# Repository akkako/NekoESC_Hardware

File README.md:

# NekoESC Hardware design repo

NekoESC V1 is a 4-in-1 ESC based on AM32 firmware.

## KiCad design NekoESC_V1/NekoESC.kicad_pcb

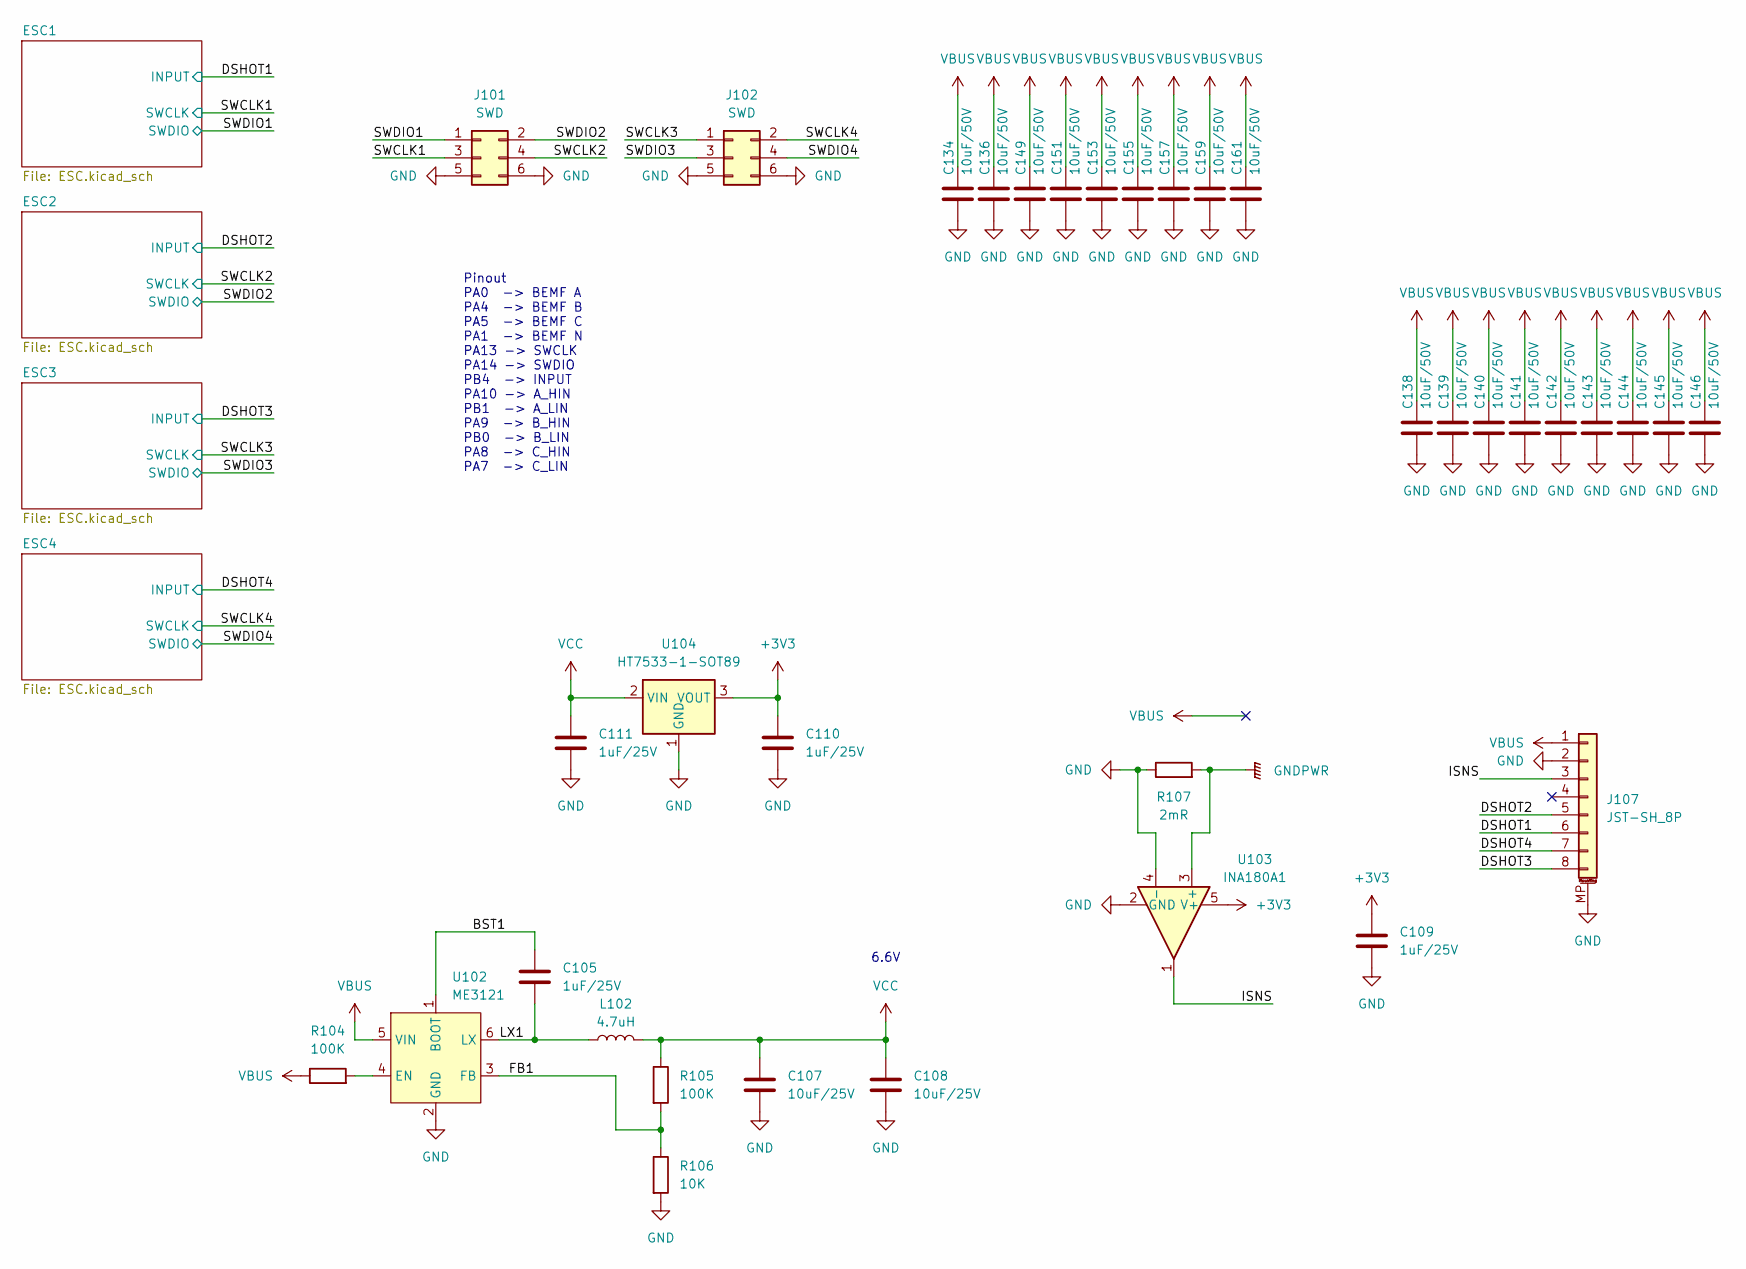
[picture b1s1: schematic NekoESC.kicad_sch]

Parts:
C105, C109, C110, C111: 1uF/25V; C_0402
C107, C108: 10uF/25V; C_0603_1608Metric
C134, C136, C138, C139, C140, C141, C142, C143, C144, C145, C146, C149, C151, C153, C155, C157, C159, C161: 10uF/50V; C_1206
J101, J102: SWD; PinHeader_2x03_P1.27mm_Vertical
J107: JST-SH_8P; JST_SH_SM08B-SRSS-TB_1x08-1MP_P1.00mm_Horizontal
L102: 4.7uH; L_Sunlord_SWPA3015S
R104, R105: 100K; R_0402
R106: 10K; R_0402
R107: 2mR; R_1206_3216Metric
U102: ME3121; SOT-23-6
U103: INA180A1; SOT-23-5
U104: HT7533-1-SOT89; SOT-89-3

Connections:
+3V3: C109.1, C110.1, U103.5 (V+), U104.3 (VOUT); also elsewhere on the board
/BST1: C105.1, U102.1 (BOOT)
/DSHOT1: J107.6; also elsewhere on the board
/DSHOT2: J107.5; also elsewhere on the board
/DSHOT3: J107.8; also elsewhere on the board
/DSHOT4: J107.7; also elsewhere on the board
/FB1: R105.2, R106.1, U102.3 (FB)
/ISNS: J107.3, U103.1
/LX1: C105.2, L102.1, U102.6 (LX)
/SWCLK1: J101.3; also elsewhere on the board
/SWCLK2: J101.4; also elsewhere on the board
/SWCLK3: J102.1; also elsewhere on the board
/SWCLK4: J102.2; also elsewhere on the board
/SWDIO1: J101.1; also elsewhere on the board
/SWDIO2: J101.2; also elsewhere on the board
/SWDIO3: J102.3; also elsewhere on the board
/SWDIO4: J102.4; also elsewhere on the board
GND: C107.2, C108.2, C109.2, C110.2, C111.2, C134.2, C136.2, C138.2, C139.2, C140.2, C141.2, C142.2, C143.2, C144.2, C145.2, C146.2, C149.2, C151.2, C153.2, C155.2, C157.2, C159.2, C161.2, J101.5, J101.6, J102.5, J102.6, J107.2, J107.MP (MountPin), R106.2, R107.1, U102.2 (GND), U103.2 (GND), U103.4 (-), U104.1 (GND); also elsewhere on the board
GNDPWR: R107.2, U103.3 (+)
unnamed: R104.2, U102.4 (EN)
VBUS: C134.1, C136.1, C138.1, C139.1, C140.1, C141.1, C142.1, C143.1, C144.1, C145.1, C146.1, C149.1, C151.1, C153.1, C155.1, C157.1, C159.1, C161.1, J107.1, R104.1, U102.5 (VIN); also elsewhere on the board
VCC: C107.1, C108.1, C111.1, L102.2, R105.1, U104.2 (VIN); also elsewhere on the board

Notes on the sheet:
6.6V
Pinout PA0 -> BEMF A PA4 -> BEMF B PA5 -> BEMF C PA1 -> BEMF N PA13 -> SWCLK PA14 -> SWDIO PB4 -> INPUT PA10 -> A_HIN PB1 -> A_LIN PA9 -> B_HIN PB0 -> B_LIN PA8 -> C_HIN PA7 -> C_LIN

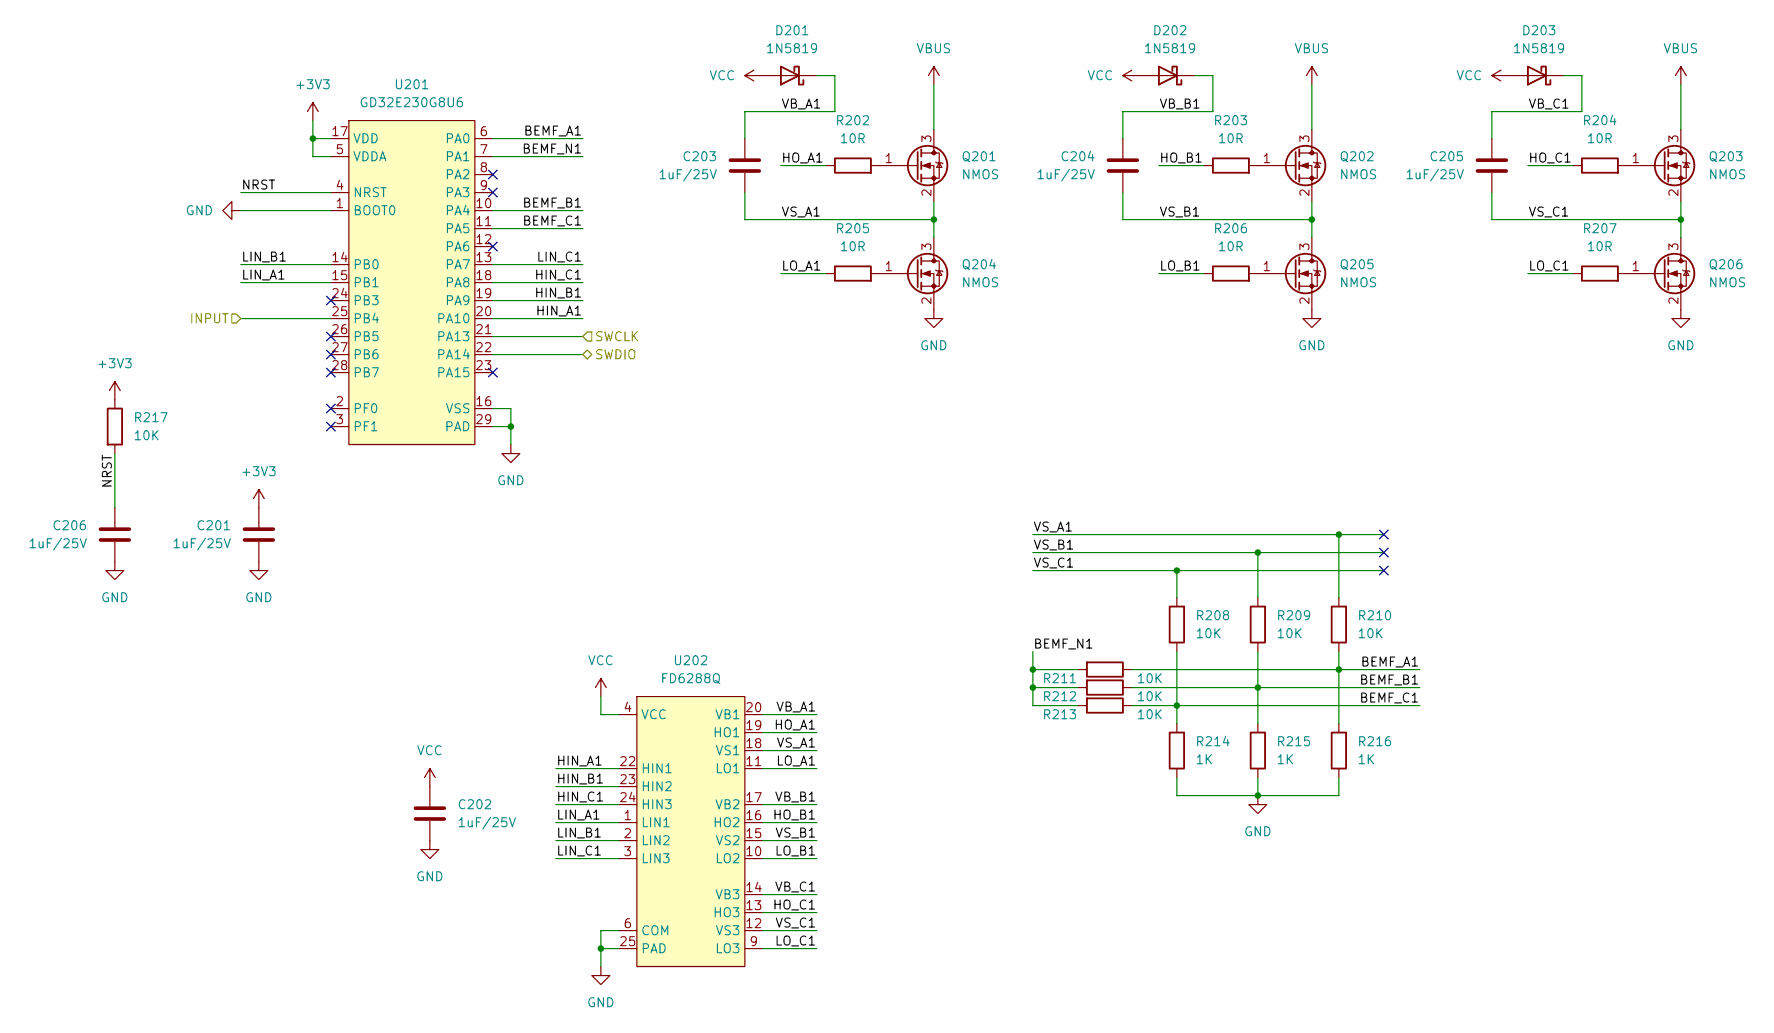
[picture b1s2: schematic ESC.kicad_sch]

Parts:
C201, C202, C203, C204, C205, C206: 1uF/25V; C_0402
D201, D202, D203: 1N5819; D_SOD-323
Q201, Q202, Q203, Q204, Q205, Q206: NMOS; DFN-8_3x3_MOS_GSD
R202, R203, R204, R205, R206, R207: 10R; R_0402
R208, R209, R210, R211, R212, R213, R217: 10K; R_0402
R214, R215, R216: 1K; R_0402
U201: GD32E230G8U6; WQFN-28-1EP_4x4mm_P0.4mm_EP2.7x2.7mm
U202: FD6288Q; QFN-24-1EP_4x4mm_P0.5mm_EP2.7x2.7mm

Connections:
+3V3: C201.1, R217.1, U201.5 (VDDA), U201.17 (VDD); also elsewhere on the board
/DSHOT1: U201.25 (PB4); also elsewhere on the board
/ESC1/BEMF_A1: R210.1, R211.1, R216.2, U201.6 (PA0)
/ESC1/BEMF_B1: R209.1, R212.1, R215.2, U201.10 (PA4)
/ESC1/BEMF_C1: R208.1, R213.1, R214.2, U201.11 (PA5)
/ESC1/BEMF_N1: R211.2, R212.2, R213.2, U201.7 (PA1)
/ESC1/HIN_A1: U201.20 (PA10), U202.22 (HIN1)
/ESC1/HIN_B1: U201.19 (PA9), U202.23 (HIN2)
/ESC1/HIN_C1: U201.18 (PA8), U202.24 (HIN3)
/ESC1/HO_A1: R202.1, U202.19 (HO1)
/ESC1/HO_B1: R203.1, U202.16 (HO2)
/ESC1/HO_C1: R204.1, U202.13 (HO3)
/ESC1/LIN_A1: U201.15 (PB1), U202.1 (LIN1)
/ESC1/LIN_B1: U201.14 (PB0), U202.2 (LIN2)
/ESC1/LIN_C1: U201.13 (PA7), U202.3 (LIN3)
/ESC1/LO_A1: R205.1, U202.11 (LO1)
/ESC1/LO_B1: R206.1, U202.10 (LO2)
/ESC1/LO_C1: R207.1, U202.9 (LO3)
/ESC1/NRST: C206.1, R217.2, U201.4 (NRST)
/ESC1/VB_A1: C203.1, D201.1 (K), U202.20 (VB1)
/ESC1/VB_B1: C204.1, D202.1 (K), U202.17 (VB2)
/ESC1/VB_C1: C205.1, D203.1 (K), U202.14 (VB3)
/ESC1/VS_A1: C203.2, Q201.2 (S), Q204.3 (D), R210.2, U202.18 (VS1)
/ESC1/VS_B1: C204.2, Q202.2 (S), Q205.3 (D), R209.2, U202.15 (VS2)
/ESC1/VS_C1: C205.2, Q203.2 (S), Q206.3 (D), R208.2, U202.12 (VS3)
/SWCLK1: U201.21 (PA13); also elsewhere on the board
/SWDIO1: U201.22 (PA14); also elsewhere on the board
GND: C201.2, C202.2, C206.2, Q204.2 (S), Q205.2 (S), Q206.2 (S), R214.1, R215.1, R216.1, U201.1 (BOOT0), U201.16 (VSS), U201.29 (PAD), U202.6 (COM), U202.25 (PAD); also elsewhere on the board
unnamed: Q201.1 (G), R202.2
unnamed: Q202.1 (G), R203.2
unnamed: Q203.1 (G), R204.2
unnamed: Q204.1 (G), R205.2
unnamed: Q205.1 (G), R206.2
unnamed: Q206.1 (G), R207.2
VBUS: Q201.3 (D), Q202.3 (D), Q203.3 (D); also elsewhere on the board
VCC: C202.1, D201.2 (A), D202.2 (A), D203.2 (A), U202.4 (VCC); also elsewhere on the board

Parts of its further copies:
C301, C302, C303, C304, C305, C306, C401, C402, C403, C404, C405, C406, C501, C502, C503, C504, C505, C506: 1uF/25V; C_0402
D301, D302, D303, D401, D402, D403, D501, D502, D503: 1N5819; D_SOD-323
Q301, Q302, Q303, Q304, Q305, Q306, Q401, Q402, Q403, Q404, Q405, Q406, Q501, Q502, Q503, Q504, Q505, Q506: NMOS; DFN-8_3x3_MOS_GSD
R218, R219, R220, R308, R309, R310, R311, R312, R313, R408, R409, R410, R411, R412, R413, R508, R509, R510, R511, R512, R513: 10K; R_0402
R301, R302, R303, R305, R306, R307, R401, R402, R403, R405, R406, R407, R501, R502, R503, R505, R506, R507: 10R; R_0402
R314, R315, R316, R414, R415, R416, R514, R515, R516: 1K; R_0402
U301, U401, U501: GD32E230G8U6; WQFN-28-1EP_4x4mm_P0.4mm_EP2.7x2.7mm
U302, U402, U502: FD6288Q; QFN-24-1EP_4x4mm_P0.5mm_EP2.7x2.7mm

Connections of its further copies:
+3V3: C304.1, C404.1, C504.1, R218.1, R219.1, R220.1, U301.5 (VDDA), U301.17 (VDD), U401.5 (VDDA), U401.17 (VDD), U501.5 (VDDA), U501.17 (VDD); also elsewhere on the board
/DSHOT2: U301.25 (PB4); also elsewhere on the board
/DSHOT3: U401.25 (PB4); also elsewhere on the board
/DSHOT4: U501.25 (PB4); also elsewhere on the board
/ESC2/BEMF_A1: R310.1, R311.1, R316.2, U301.6 (PA0)
/ESC2/BEMF_B1: R309.1, R312.1, R315.2, U301.10 (PA4)
/ESC2/BEMF_C1: R308.1, R313.1, R314.2, U301.11 (PA5)
/ESC2/BEMF_N1: R311.2, R312.2, R313.2, U301.7 (PA1)
/ESC2/HIN_A1: U301.20 (PA10), U302.22 (HIN1)
/ESC2/HIN_B1: U301.19 (PA9), U302.23 (HIN2)
/ESC2/HIN_C1: U301.18 (PA8), U302.24 (HIN3)
/ESC2/HO_A1: R301.1, U302.19 (HO1)
/ESC2/HO_B1: R302.1, U302.16 (HO2)
/ESC2/HO_C1: R303.1, U302.13 (HO3)
/ESC2/LIN_A1: U301.15 (PB1), U302.1 (LIN1)
/ESC2/LIN_B1: U301.14 (PB0), U302.2 (LIN2)
/ESC2/LIN_C1: U301.13 (PA7), U302.3 (LIN3)
/ESC2/LO_A1: R305.1, U302.11 (LO1)
/ESC2/LO_B1: R306.1, U302.10 (LO2)
/ESC2/LO_C1: R307.1, U302.9 (LO3)
/ESC2/NRST: C306.1, R218.2, U301.4 (NRST)
/ESC2/VB_A1: C301.1, D301.1 (K), U302.20 (VB1)
/ESC2/VB_B1: C302.1, D302.1 (K), U302.17 (VB2)
/ESC2/VB_C1: C303.1, D303.1 (K), U302.14 (VB3)
/ESC2/VS_A1: C301.2, Q301.2 (S), Q304.3 (D), R310.2, U302.18 (VS1)
/ESC2/VS_B1: C302.2, Q302.2 (S), Q305.3 (D), R309.2, U302.15 (VS2)
/ESC2/VS_C1: C303.2, Q303.2 (S), Q306.3 (D), R308.2, U302.12 (VS3)
/ESC3/BEMF_A1: R410.1, R411.1, R416.2, U401.6 (PA0)
/ESC3/BEMF_B1: R409.1, R412.1, R415.2, U401.10 (PA4)
/ESC3/BEMF_C1: R408.1, R413.1, R414.2, U401.11 (PA5)
/ESC3/BEMF_N1: R411.2, R412.2, R413.2, U401.7 (PA1)
/ESC3/HIN_A1: U401.20 (PA10), U402.22 (HIN1)
/ESC3/HIN_B1: U401.19 (PA9), U402.23 (HIN2)
/ESC3/HIN_C1: U401.18 (PA8), U402.24 (HIN3)
/ESC3/HO_A1: R401.1, U402.19 (HO1)
/ESC3/HO_B1: R402.1, U402.16 (HO2)
/ESC3/HO_C1: R403.1, U402.13 (HO3)
/ESC3/LIN_A1: U401.15 (PB1), U402.1 (LIN1)
/ESC3/LIN_B1: U401.14 (PB0), U402.2 (LIN2)
/ESC3/LIN_C1: U401.13 (PA7), U402.3 (LIN3)
/ESC3/LO_A1: R405.1, U402.11 (LO1)
/ESC3/LO_B1: R406.1, U402.10 (LO2)
/ESC3/LO_C1: R407.1, U402.9 (LO3)
/ESC3/NRST: C406.1, R219.2, U401.4 (NRST)
/ESC3/VB_A1: C401.1, D401.1 (K), U402.20 (VB1)
/ESC3/VB_B1: C402.1, D402.1 (K), U402.17 (VB2)
/ESC3/VB_C1: C403.1, D403.1 (K), U402.14 (VB3)
/ESC3/VS_A1: C401.2, Q401.2 (S), Q404.3 (D), R410.2, U402.18 (VS1)
/ESC3/VS_B1: C402.2, Q402.2 (S), Q405.3 (D), R409.2, U402.15 (VS2)
/ESC3/VS_C1: C403.2, Q403.2 (S), Q406.3 (D), R408.2, U402.12 (VS3)
/ESC4/BEMF_A1: R510.1, R511.1, R516.2, U501.6 (PA0)
/ESC4/BEMF_B1: R509.1, R512.1, R515.2, U501.10 (PA4)
/ESC4/BEMF_C1: R508.1, R513.1, R514.2, U501.11 (PA5)
/ESC4/BEMF_N1: R511.2, R512.2, R513.2, U501.7 (PA1)
/ESC4/HIN_A1: U501.20 (PA10), U502.22 (HIN1)
/ESC4/HIN_B1: U501.19 (PA9), U502.23 (HIN2)
/ESC4/HIN_C1: U501.18 (PA8), U502.24 (HIN3)
/ESC4/HO_A1: R501.1, U502.19 (HO1)
/ESC4/HO_B1: R502.1, U502.16 (HO2)
/ESC4/HO_C1: R503.1, U502.13 (HO3)
/ESC4/LIN_A1: U501.15 (PB1), U502.1 (LIN1)
/ESC4/LIN_B1: U501.14 (PB0), U502.2 (LIN2)
/ESC4/LIN_C1: U501.13 (PA7), U502.3 (LIN3)
/ESC4/LO_A1: R505.1, U502.11 (LO1)
/ESC4/LO_B1: R506.1, U502.10 (LO2)
/ESC4/LO_C1: R507.1, U502.9 (LO3)
/ESC4/NRST: C506.1, R220.2, U501.4 (NRST)
/ESC4/VB_A1: C501.1, D501.1 (K), U502.20 (VB1)
/ESC4/VB_B1: C502.1, D502.1 (K), U502.17 (VB2)
/ESC4/VB_C1: C503.1, D503.1 (K), U502.14 (VB3)
/ESC4/VS_A1: C501.2, Q501.2 (S), Q504.3 (D), R510.2, U502.18 (VS1)
/ESC4/VS_B1: C502.2, Q502.2 (S), Q505.3 (D), R509.2, U502.15 (VS2)
/ESC4/VS_C1: C503.2, Q503.2 (S), Q506.3 (D), R508.2, U502.12 (VS3)
/SWCLK2: U301.21 (PA13); also elsewhere on the board
/SWCLK3: U401.21 (PA13); also elsewhere on the board
/SWCLK4: U501.21 (PA13); also elsewhere on the board
/SWDIO2: U301.22 (PA14); also elsewhere on the board
/SWDIO3: U401.22 (PA14); also elsewhere on the board
/SWDIO4: U501.22 (PA14); also elsewhere on the board
GND: C304.2, C305.2, C306.2, C404.2, C405.2, C406.2, C504.2, C505.2, C506.2, Q304.2 (S), Q305.2 (S), Q306.2 (S), Q404.2 (S), Q405.2 (S), Q406.2 (S), Q504.2 (S), Q505.2 (S), Q506.2 (S), R314.1, R315.1, R316.1, R414.1, R415.1, R416.1, R514.1, R515.1, R516.1, U301.1 (BOOT0), U301.16 (VSS), U301.29 (PAD), U302.6 (COM), U302.25 (PAD), U401.1 (BOOT0), U401.16 (VSS), U401.29 (PAD), U402.6 (COM), U402.25 (PAD), U501.1 (BOOT0), U501.16 (VSS), U501.29 (PAD), U502.6 (COM), U502.25 (PAD); also elsewhere on the board
unnamed: Q301.1 (G), R301.2
unnamed: Q302.1 (G), R302.2
unnamed: Q303.1 (G), R303.2
unnamed: Q304.1 (G), R305.2
unnamed: Q305.1 (G), R306.2
unnamed: Q306.1 (G), R307.2
unnamed: Q401.1 (G), R401.2
unnamed: Q402.1 (G), R402.2
unnamed: Q403.1 (G), R403.2
unnamed: Q404.1 (G), R405.2
unnamed: Q405.1 (G), R406.2
unnamed: Q406.1 (G), R407.2
unnamed: Q501.1 (G), R501.2
unnamed: Q502.1 (G), R502.2
unnamed: Q503.1 (G), R503.2
unnamed: Q504.1 (G), R505.2
unnamed: Q505.1 (G), R506.2
unnamed: Q506.1 (G), R507.2
VBUS: Q301.3 (D), Q302.3 (D), Q303.3 (D), Q401.3 (D), Q402.3 (D), Q403.3 (D), Q501.3 (D), Q502.3 (D), Q503.3 (D); also elsewhere on the board
VCC: C305.1, C405.1, C505.1, D301.2 (A), D302.2 (A), D303.2 (A), D401.2 (A), D402.2 (A), D403.2 (A), D501.2 (A), D502.2 (A), D503.2 (A), U302.4 (VCC), U402.4 (VCC), U502.4 (VCC); also elsewhere on the board

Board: 4 copper layers, 167 parts (146 on the bottom side), 138 nets, no tracks yet.

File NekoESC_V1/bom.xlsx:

Reference | Value | Footprint | Qty | JLC Part Number | 类型 | 优信电子
C101 | 1uF/50V | Capacitor_SMD:C_0603_1608Metric | 1 | C15849 | 基础库
C105,C109,C110,C111,C201,C202,C203,C204,C205,C206,C301,C302,C303,C304,C305,C306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 | 1uF/25V | Capacitor_SMD:C_0402_1005Metric | 28 | C52923 | 基础库
C107,C108 | 10uF/25V | Capacitor_SMD:C_0603_1608Metric | 2 | C96446 | 基础库
C122,C123,C124,C125,C126,C127,C128,C129,C130,C131,C133,C134,C135,C136,C138,C139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 | 10uF/50V | Capacitor_SMD:C_1206_3216Metric | 40 | C13585 | 基础库
D201,D202,D203,D301,D302,D303,D401,D402,D403,D501,D502,D503 | RB521S-30 | Diode_SMD:D_SOD-523 | 12 | C7502702 | 扩展库 | https://item.taobao.com/item.htm?id=578704865069&spm=a1z10.3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
J101,J102 | SWD | Connector_PinHeader_1.27mm:PinHeader_2x03_P1.27mm_Vertical | 2 | NC
J107 | JST-SH_8P | Connector_JST:JST_SH_SM08B-SRSS-TB_1x08-1MP_P1.00mm_Horizontal | 1 | C22461263 | 扩展库 | https://item.taobao.com/item.htm?id=565715285795&pisk=gooSl7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
L102 | 4.7uH | Inductor_SMD:L_Sunlord_SWPA3015S | 1 |  | 扩展库 | https://item.taobao.com/item.htm?id=588985051069&pisk=g2AE-h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
Q201,Q202,Q203,Q204,Q205,Q206,Q301,Q302,Q303,Q304,Q305,Q306,Q401,Q402,Q403,Q404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 | NMOS | myLib:DFN8_3x3_MOS_GSD | 24
R104,R105 | 100K | Resistor_SMD:R_0402_1005Metric | 2 | C25741 | 基础库
R106,R201,R208,R209,R210,R211,R212,R213,R304,R308,R309,R310,R311,R312,R313,R404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 | 10K | Resistor_SMD:R_0402_1005Metric | 29 | C25744 | 基础库
R107 | 2mR | Resistor_SMD:R_1218_3246Metric | 1
R202,R203,R204,R205,R206,R207,R301,R302,R303,R305,R306,R307,R401,R402,R403,R405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 | 10R | Resistor_SMD:R_0402_1005Metric | 24 | C25077 | 基础库
R214,R215,R216,R314,R315,R316,R414,R415,R416,R514,R515,R516 | 1K | Resistor_SMD:R_0402_1005Metric | 12 | C11702 | 基础库
U102 | ME3121 | Package_TO_SOT_SMD:SOT-23-6 | 1 | C2932938 | 扩展库 | https://item.taobao.com/item.htm?id=820731749644&pisk=gqIx5Y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
U103 | INA180A2 | Package_TO_SOT_SMD:SOT-23-5 | 1 | C192764 | 扩展库 | https://item.taobao.com/item.htm?id=855044941588&pisk=gdVi-m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
U104 | HT7533-1-SOT89 | Package_TO_SOT_SMD:SOT-89-3 | 1 | C14289 | 基础库
U201,U301,U401,U501 | GD32E230G8U6 | Package_DFN_QFN:QFN-28-1EP_4x4mm_P0.4mm_EP2.8x2.8mm | 4 | C380534 | 扩展库
U202,U302,U402,U502 | FD6288Q | Package_DFN_QFN:QFN-24-1EP_4x4mm_P0.5mm_EP2.7x2.7mm | 4 | C328453 | 扩展库

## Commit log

2025-09-29 add project
2025-09-29 add libs
2025-09-29 add c1206
2025-09-29 smaller
2025-09-29 update lib
2025-09-29 modify hardware
